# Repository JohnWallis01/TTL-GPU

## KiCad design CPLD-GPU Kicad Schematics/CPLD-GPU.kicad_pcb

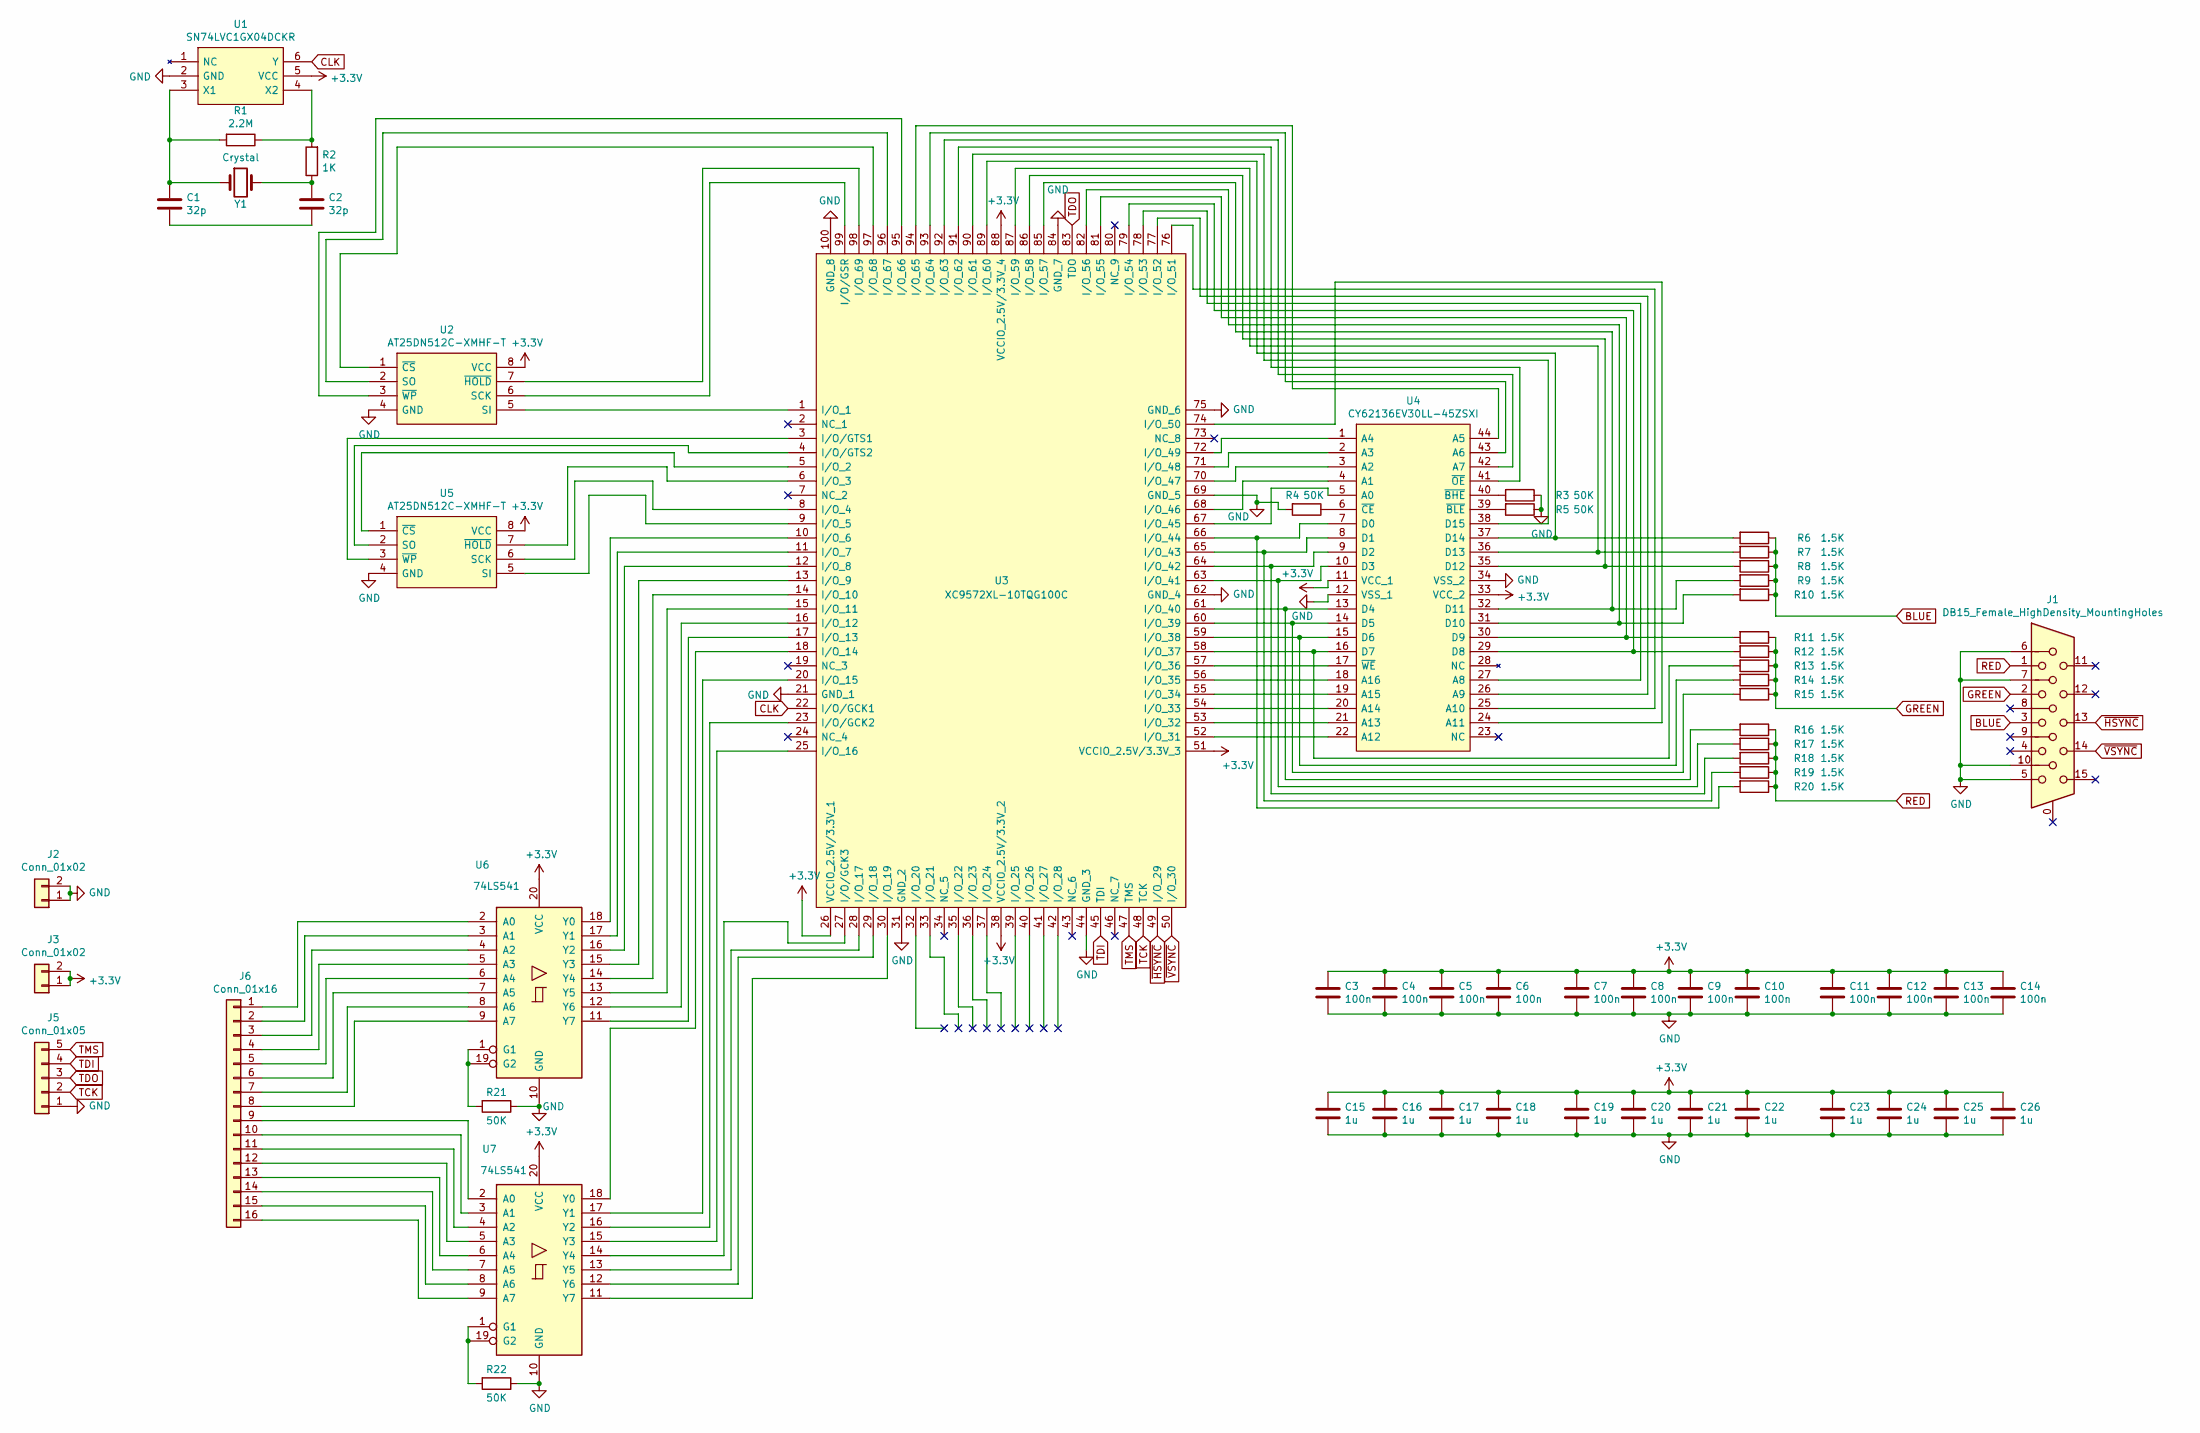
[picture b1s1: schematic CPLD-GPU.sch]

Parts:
C1, C2: 32p; C_0805_2012Metric
C3, C4, C5, C6, C7, C8, C9, C10, C11, C12, C13, C14: 100n; C_0805_2012Metric
C15, C16, C17, C18, C19, C20, C21, C22, C23, C24, C25, C26: 1u; C_0805_2012Metric
J1: DB15_Female_HighDensity_MountingHoles; DSUB-15_Female_Horizontal_P2.77x2.84mm_EdgePinOffset4.94mm_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
J2, J3: Conn_01x02; PinHeader_1x02_P2.54mm_Vertical
J5: Conn_01x05; PinHeader_1x05_P2.54mm_Vertical
J6: Conn_01x16; PinHeader_1x16_P2.54mm_Vertical
R1: 2.2M; R_0805_2012Metric
R2: 1K; R_0805_2012Metric
R3, R4, R5, R21, R22: 50K; R_0805_2012Metric
R6, R7, R8, R9, R10, R11, R12, R13, R14, R15, R16, R17, R18, R19, R20: 1.5K; R_0805_2012Metric
U1: SN74LVC1GX04DCKR; SOT-363_SC-70-6_Handsoldering; Mouser Part Number 595-SN74LVC1GX04DCKR
U2, U5: AT25DN512C-XMHF-T; SSOP-8_2.95x2.8mm_P0.65mm; Manufacturer_Part_Number AT25DN512C-XMHF-T
U3: XC9572XL-10TQG100C; TQFP-100_14x14mm_P0.5mm; Mouser Part Number 217-9572XL-10TQG100C
U4: CY62136EV30LL-45ZSXI; TSOP-II-44_10.16x18.41mm_P0.8mm; Manufacturer_Part_Number CY62136EV30LL-45ZSXI
U6, U7: 74LS541; TSSOP-20_4.4x6.5mm_P0.65mm
Y1: Crystal; Crystal_HC49-4H_Vertical

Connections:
+3V3: C3.1, C4.1, C5.1, C6.1, C7.1, C8.1, C9.1, C10.1, C11.1, C12.1, C13.1, C14.1, C15.1, C16.1, C17.1, C18.1, C19.1, C20.1, C21.1, C22.1, C23.1, C24.1, C25.1, C26.1, J3.1, J3.2, U1.5 (VCC), U2.8 (VCC), U3.26 (VCCIO_2.5V/3.3V_1), U3.38 (VCCIO_2.5V/3.3V_2), U3.51 (VCCIO_2.5V/3.3V_3), U3.88 (VCCIO_2.5V/3.3V_4), U4.11 (VCC_1), U4.33 (VCC_2), U5.8 (VCC), U6.20 (VCC), U7.20 (VCC)
BLUE: J1.3, R6.1, R7.1, R8.1, R9.1, R10.1
CLK: U1.6 (Y), U3.22 (I/O/GCK1)
GND: C3.2, C4.2, C5.2, C6.2, C7.2, C8.2, C9.2, C10.2, C11.2, C12.2, C13.2, C14.2, C15.2, C16.2, C17.2, C18.2, C19.2, C20.2, C21.2, C22.2, C23.2, C24.2, C25.2, C26.2, J1.5, J1.6, J1.7, J1.10, J2.1, J2.2, J5.1, R3.1, R4.2, R5.1, R21.1, R22.1, U1.2 (GND), U2.4 (GND), U3.21 (GND_1), U3.31 (GND_2), U3.44 (GND_3), U3.62 (GND_4), U3.69 (GND_5), U3.75 (GND_6), U3.84 (GND_7), U3.100 (GND_8), U4.12 (VSS_1), U4.34 (VSS_2), U5.4 (GND), U6.10 (GND), U7.10 (GND)
GREEN: J1.2, R11.1, R12.1, R13.1, R14.1, R15.1
unnamed: C1.1, R1.2, U1.3 (X1), Y1.1
unnamed: C1.2, C2.2
unnamed: C2.1, R2.1, Y1.2
unnamed: J6.1, U6.2 (A0)
unnamed: J6.2, U6.3 (A1)
unnamed: J6.3, U6.4 (A2)
unnamed: J6.4, U6.5 (A3)
unnamed: J6.5, U6.6 (A4)
unnamed: J6.6, U6.7 (A5)
unnamed: J6.7, U6.8 (A6)
unnamed: J6.8, U6.9 (A7)
unnamed: J6.9, U7.2 (A0)
unnamed: J6.10, U7.3 (A1)
unnamed: J6.11, U7.4 (A2)
unnamed: J6.12, U7.5 (A3)
unnamed: J6.13, U7.6 (A4)
unnamed: J6.14, U7.7 (A5)
unnamed: J6.15, U7.8 (A6)
unnamed: J6.16, U7.9 (A7)
unnamed: R1.1, R2.2, U1.4 (X2)
unnamed: R3.2, U4.40 (~BHE)
unnamed: R4.1, U4.6 (~CE)
unnamed: R5.2, U4.39 (~BLE)
unnamed: R6.2, U3.89 (I/O_60), U4.37 (D14)
unnamed: R7.2, U3.87 (I/O_59), U4.36 (D13)
unnamed: R8.2, U3.86 (I/O_58), U4.35 (D12)
unnamed: R9.2, U3.85 (I/O_57), U4.32 (D11)
unnamed: R10.2, U3.82 (I/O_56), U4.31 (D10)
unnamed: R11.2, U3.81 (I/O_55), U4.30 (D9)
unnamed: R12.2, U3.79 (I/O_54), U4.29 (D8)
unnamed: R13.2, U3.58 (I/O_37), U4.16 (D7)
unnamed: R14.2, U3.59 (I/O_38), U4.15 (D6)
unnamed: R15.2, U3.60 (I/O_39), U4.14 (D5)
unnamed: R16.2, U3.61 (I/O_40), U4.13 (D4)
unnamed: R17.2, U3.63 (I/O_41), U4.10 (D3)
unnamed: R18.2, U3.64 (I/O_42), U4.9 (D2)
unnamed: R19.2, U3.65 (I/O_43), U4.8 (D1)
unnamed: R20.2, U3.66 (I/O_44), U4.7 (D0)
unnamed: R21.2, U6.1 (G1), U6.19 (G2)
unnamed: R22.2, U7.1 (G1), U7.19 (G2)
unnamed: U2.1 (~CS), U3.97 (I/O_68)
unnamed: U2.2 (SO), U3.96 (I/O_67)
unnamed: U2.3 (~WP), U3.95 (I/O_66)
unnamed: U2.5 (SI), U3.1 (I/O_1)
unnamed: U2.6 (SCK), U3.99 (I/O/GSR)
unnamed: U2.7 (~HOLD), U3.98 (I/O_69)
unnamed: U3.3 (I/O/GTS1), U5.3 (~WP)
unnamed: U3.4 (I/O/GTS2), U5.2 (SO)
unnamed: U3.5 (I/O_2), U5.1 (~CS)
unnamed: U3.6 (I/O_3), U5.7 (~HOLD)
unnamed: U3.8 (I/O_4), U5.6 (SCK)
unnamed: U3.9 (I/O_5), U5.5 (SI)
unnamed: U3.10 (I/O_6), U6.18 (Y0)
unnamed: U3.11 (I/O_7), U6.17 (Y1)
unnamed: U3.12 (I/O_8), U6.16 (Y2)
unnamed: U3.13 (I/O_9), U6.15 (Y3)
unnamed: U3.14 (I/O_10), U6.14 (Y4)
unnamed: U3.15 (I/O_11), U6.13 (Y5)
unnamed: U3.16 (I/O_12), U6.12 (Y6)
unnamed: U3.17 (I/O_13), U6.11 (Y7)
unnamed: U3.18 (I/O_14), U7.18 (Y0)
unnamed: U3.20 (I/O_15), U7.17 (Y1)
unnamed: U3.23 (I/O/GCK2), U7.16 (Y2)
unnamed: U3.25 (I/O_16), U7.15 (Y3)
unnamed: U3.27 (I/O/GCK3), U7.14 (Y4)
unnamed: U3.28 (I/O_17), U7.13 (Y5)
unnamed: U3.29 (I/O_18), U7.12 (Y6)
unnamed: U3.30 (I/O_19), U7.11 (Y7)
unnamed: U3.52 (I/O_31), U4.22 (A12)
unnamed: U3.53 (I/O_32), U4.21 (A13)
unnamed: U3.54 (I/O_33), U4.20 (A14)
unnamed: U3.55 (I/O_34), U4.19 (A15)
unnamed: U3.56 (I/O_35), U4.18 (A16)
unnamed: U3.57 (I/O_36), U4.17 (~WE)
unnamed: U3.67 (I/O_45), U4.5 (A0)
unnamed: U3.68 (I/O_46), U4.4 (A1)
unnamed: U3.70 (I/O_47), U4.3 (A2)
unnamed: U3.71 (I/O_48), U4.2 (A3)
unnamed: U3.72 (I/O_49), U4.1 (A4)
unnamed: U3.74 (I/O_50), U4.24 (A11)
unnamed: U3.76 (I/O_51), U4.25 (A10)
unnamed: U3.77 (I/O_52), U4.26 (A9)
unnamed: U3.78 (I/O_53), U4.27 (A8)
unnamed: U3.90 (I/O_61), U4.38 (D15)
unnamed: U3.91 (I/O_62), U4.41 (~OE)
unnamed: U3.92 (I/O_63), U4.42 (A7)
unnamed: U3.93 (I/O_64), U4.43 (A6)
unnamed: U3.94 (I/O_65), U4.44 (A5)
RED: J1.1, R16.1, R17.1, R18.1, R19.1, R20.1
TCK: J5.2, U3.48 (TCK)
TDI: J5.4, U3.45 (TDI)
TDO: J5.3, U3.83 (TDO)
TMS: J5.5, U3.47 (TMS)
~HSYNC: J1.13, U3.49 (I/O_29)
~VSYNC: J1.14, U3.50 (I/O_30)

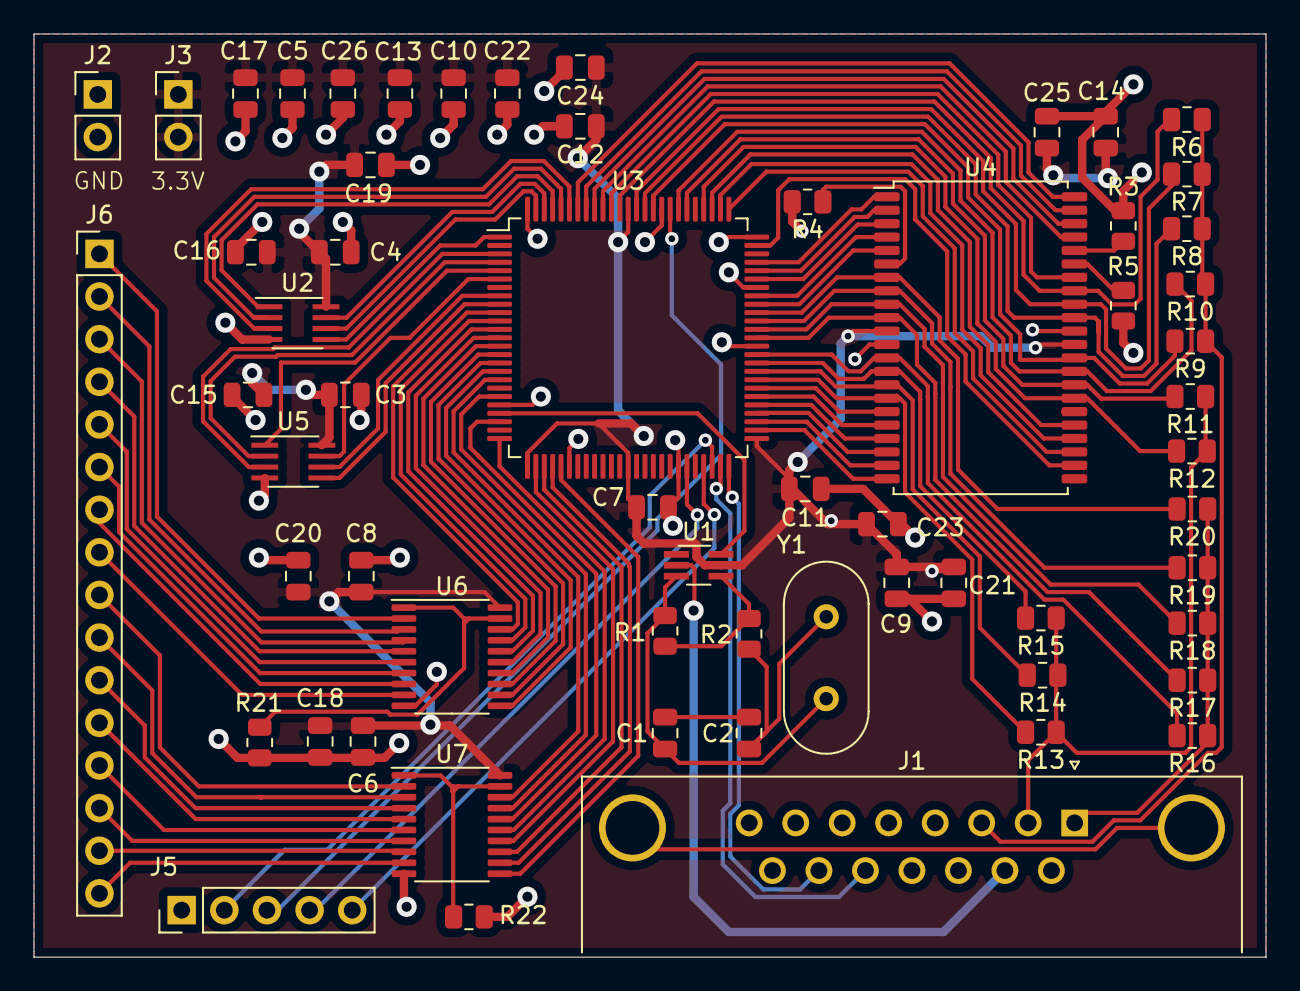
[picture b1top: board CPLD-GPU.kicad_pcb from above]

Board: 2 copper layers, 73.4 x 55.0 mm, 61 parts (0 on the bottom side), 100 nets.

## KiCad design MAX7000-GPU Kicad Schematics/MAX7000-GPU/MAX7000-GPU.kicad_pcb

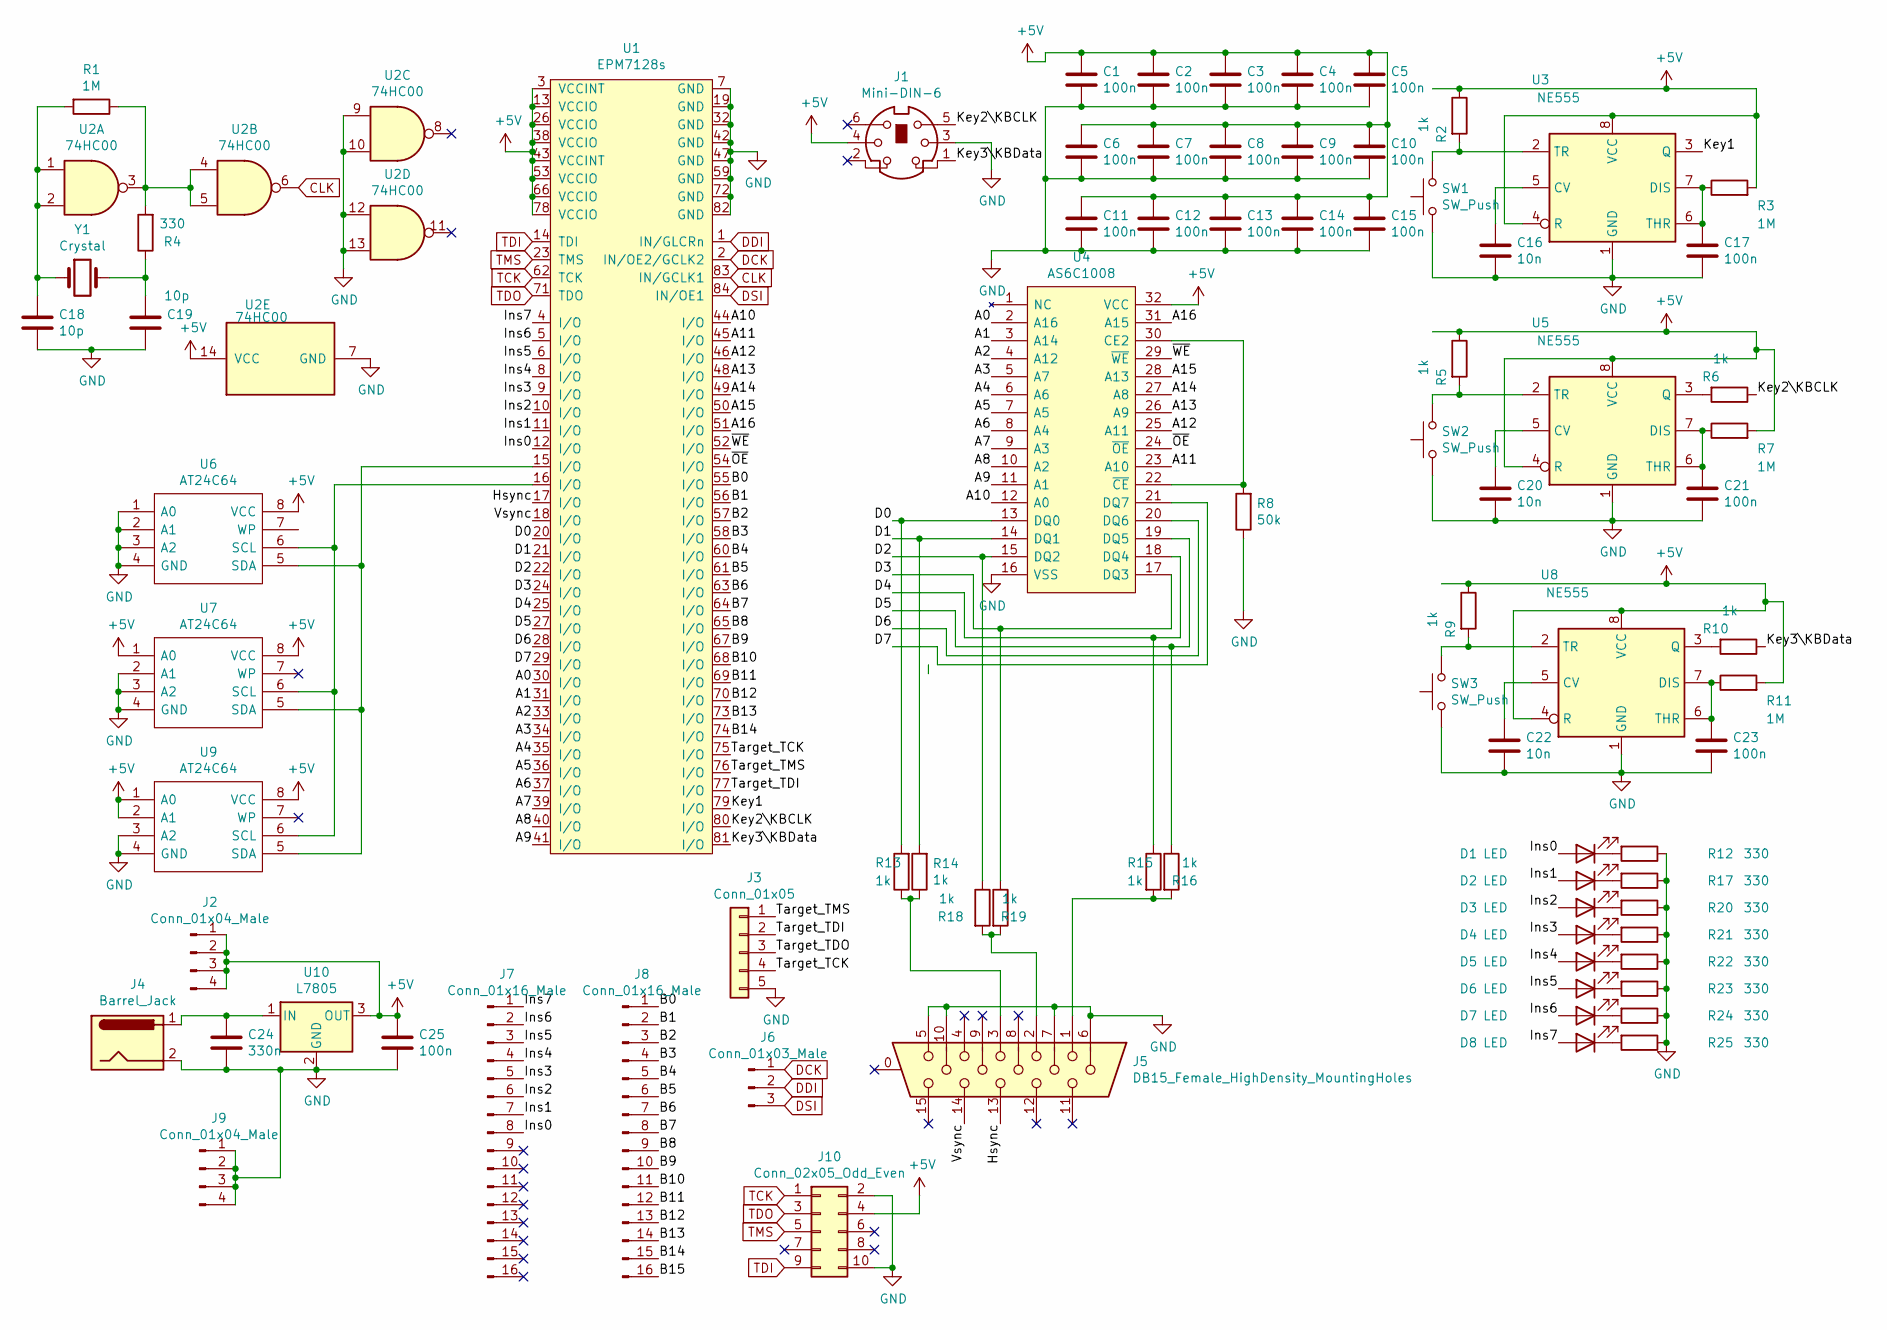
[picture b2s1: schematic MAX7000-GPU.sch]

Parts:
C1, C2, C3, C4, C5, C6, C7, C8, C9, C10, C11, C12, C13, C14, C15, C17, C21, C23, C25: 100n; C_0805_2012Metric
C16, C20, C22: 10n; C_0805_2012Metric
C18, C19: 10p; C_0805_2012Metric
C24: 330n; C_0805_2012Metric
D1, D2, D3, D4, D5, D6, D7, D8: LED; LED_0805_2012Metric
J1: Mini-DIN-6; Connector_Mini-DIN_Female_6Pin_2rows
J2, J9: Conn_01x04_Male; PinSocket_1x04_P2.54mm_Vertical
J3: Conn_01x05; PinSocket_1x05_P2.54mm_Vertical
J4: Barrel_Jack; BarrelJack_Wuerth_6941xx301002
J5: DB15_Female_HighDensity_MountingHoles; DSUB-15-HD_Female_Horizontal_P2.29x1.98mm_EdgePinOffset3.03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
J6: Conn_01x03_Male; PinSocket_1x03_P2.54mm_Vertical
J7, J8: Conn_01x16_Male; PinSocket_1x16_P2.54mm_Vertical
J10: Conn_02x05_Odd_Even; PinHeader_2x05_P2.54mm_Vertical
R1, R3, R7, R11: 1M; R_0805_2012Metric
R2, R5, R6, R9, R10, R13, R14, R15, R16, R18, R19: 1k; R_0805_2012Metric
R4, R12, R17, R20, R21, R22, R23, R24, R25: 330; R_0805_2012Metric
R8: 50k; R_0805_2012Metric
SW1, SW2, SW3: SW_Push; SW_PUSH_6mm
U1: EPM7128s; PLCC-84_THT-Socket
U2: 74HC00; DIP-14_W7.62mm
U3, U5, U8: NE555; DIP-8_W7.62mm
U4: AS6C1008; DIP-32_W15.24mm; Mouser Part Number 913-AS6C1008-55PCN
U6, U7, U9: AT24C64; DIP-8_W7.62mm; Manufacturer_Part_Number AT24C64B-10PU-2.7
U10: L7805; TO-220-3_Vertical
Y1: Crystal; Crystal_HC49-U_Vertical

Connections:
+5V: C1.1, C2.1, C3.1, C4.1, C5.1, C6.1, C7.1, C8.1, C9.1, C10.1, C11.1, C12.1, C13.1, C14.1, C15.1, C25.1, J1.4, J2.1, J2.2, J2.3, J2.4, J10.4, R2.1, R3.2, R5.1, R7.2, R9.1, R11.2, U1.3 (VCCINT), U1.13 (VCCIO), U1.26 (VCCIO), U1.38 (VCCIO), U1.43 (VCCINT), U1.53 (VCCIO), U1.66 (VCCIO), U1.78 (VCCIO), U2.14 (VCC), U3.4 (R), U3.8 (VCC), U4.32 (VCC), U5.4 (R), U5.8 (VCC), U6.8 (VCC), U7.1 (A0), U7.8 (VCC), U8.4 (R), U8.8 (VCC), U9.1 (A0), U9.2 (A1), U9.8 (VCC), U10.3 (OUT)
/A0: U1.30 (I/O), U4.2 (A16)
/A1: U1.31 (I/O), U4.3 (A14)
/A2: U1.33 (I/O), U4.4 (A12)
/A3: U1.34 (I/O), U4.5 (A7)
/A4: U1.35 (I/O), U4.6 (A6)
/A5: U1.36 (I/O), U4.7 (A5)
/A6: U1.37 (I/O), U4.8 (A4)
/A7: U1.39 (I/O), U4.9 (A3)
/A8: U1.40 (I/O), U4.10 (A2)
/A9: U1.41 (I/O), U4.11 (A1)
/A10: U1.44 (I/O), U4.12 (A0)
/A11: U1.45 (I/O), U4.23 (A10)
/A12: U1.46 (I/O), U4.25 (A11)
/A13: U1.48 (I/O), U4.26 (A9)
/A14: U1.49 (I/O), U4.27 (A8)
/A15: U1.50 (I/O), U4.28 (A13)
/A16: U1.51 (I/O), U4.31 (A15)
/B0: J8.1, U1.55 (I/O)
/B1: J8.2, U1.56 (I/O)
/B2: J8.3, U1.57 (I/O)
/B3: J8.4, U1.58 (I/O)
/B4: J8.5, U1.60 (I/O)
/B5: J8.6, U1.61 (I/O)
/B6: J8.7, U1.63 (I/O)
/B7: J8.8, U1.64 (I/O)
/B8: J8.9, U1.65 (I/O)
/B9: J8.10, U1.67 (I/O)
/B10: J8.11, U1.68 (I/O)
/B11: J8.12, U1.69 (I/O)
/B12: J8.13, U1.70 (I/O)
/B13: J8.14, U1.73 (I/O)
/B14: J8.15, U1.74 (I/O)
/D0: R13.2, U1.20 (I/O), U4.13 (DQ0)
/D1: R14.2, U1.21 (I/O), U4.14 (DQ1)
/D2: R18.1, U1.22 (I/O), U4.15 (DQ2)
/D3: R19.1, U1.24 (I/O), U4.17 (DQ3)
/D4: R15.1, U1.25 (I/O), U4.18 (DQ4)
/D5: R16.1, U1.27 (I/O), U4.19 (DQ5)
/D6: U1.28 (I/O), U4.20 (DQ6)
/D7: U1.29 (I/O), U4.21 (DQ7)
/Hsync: J5.13, U1.17 (I/O)
/Ins0: D1.2 (A), J7.8, U1.12 (I/O)
/Ins1: D2.2 (A), J7.7, U1.11 (I/O)
/Ins2: D3.2 (A), J7.6, U1.10 (I/O)
/Ins3: D4.2 (A), J7.5, U1.9 (I/O)
/Ins4: D5.2 (A), J7.4, U1.8 (I/O)
/Ins5: D6.2 (A), J7.3, U1.6 (I/O)
/Ins6: D7.2 (A), J7.2, U1.5 (I/O)
/Ins7: D8.2 (A), J7.1, U1.4 (I/O)
/Key1: U1.79 (I/O), U3.3 (Q)
/Key2\KBCLK: J1.5, R6.1, U1.80 (I/O)
/Key3\KBData: J1.1, R10.1, U1.81 (I/O)
/Target_TCK: J3.4, U1.75 (I/O)
/Target_TDI: J3.2, U1.77 (I/O)
/Target_TMS: J3.1, U1.76 (I/O)
/Vsync: J5.14, U1.18 (I/O)
/~OE: U1.54 (I/O), U4.24 (~OE)
/~WE: U1.52 (I/O), U4.29 (~WE)
CLK: U1.83 (IN/GCLK1), U2.6
DCK: J6.1, U1.2 (IN/OE2/GCLK2)
DDI: J6.2, U1.1 (IN/GLCRn)
DSI: J6.3, U1.84 (IN/OE1)
GND: C1.2, C2.2, C3.2, C4.2, C5.2, C6.2, C7.2, C8.2, C9.2, C10.2, C11.2, C12.2, C13.2, C14.2, C15.2, C16.2, C17.2, C18.2, C19.2, C20.2, C21.2, C22.2, C23.2, C24.2, C25.2, J1.3, J3.5, J4.2, J5.5, J5.6, J5.7, J5.10, J9.1, J9.2, J9.3, J9.4, J10.2, J10.10, R8.1, R12.1, R17.1, R20.1, R21.1, R22.1, R23.1, R24.1, R25.1, SW1.1, SW2.1, SW3.1, U1.7 (GND), U1.19 (GND), U1.32 (GND), U1.42 (GND), U1.47 (GND), U1.59 (GND), U1.72 (GND), U1.82 (GND), U2.7 (GND), U2.9, U2.10, U2.12, U2.13, U3.1 (GND), U4.16 (VSS), U5.1 (GND), U6.1 (A0), U6.2 (A1), U6.3 (A2), U6.4 (GND), U7.2 (A1), U7.3 (A2), U7.4 (GND), U8.1 (GND), U9.3 (A2), U9.4 (GND), U10.2 (GND)
unnamed: C16.1, U3.5 (CV)
unnamed: C17.1, R3.1, U3.6 (THR), U3.7 (DIS)
unnamed: C18.1, R1.2, U2.1, U2.2, Y1.1
unnamed: C19.1, R4.1, Y1.2
unnamed: C20.1, U5.5 (CV)
unnamed: C21.1, R7.1, U5.6 (THR), U5.7 (DIS)
unnamed: C22.1, U8.5 (CV)
unnamed: C23.1, R11.1, U8.6 (THR), U8.7 (DIS)
unnamed: C24.1, J4.1, U10.1 (IN)
unnamed: D1.1 (K), R12.2
unnamed: D2.1 (K), R17.2
unnamed: D3.1 (K), R20.2
unnamed: D4.1 (K), R21.2
unnamed: D5.1 (K), R22.2
unnamed: D6.1 (K), R23.2
unnamed: D7.1 (K), R24.2
unnamed: D8.1 (K), R25.2
unnamed: J5.1, R15.2, R16.2
unnamed: J5.2, R18.2, R19.2
unnamed: J5.3, R13.1, R14.1
unnamed: R1.1, R4.2, U2.3, U2.4, U2.5
unnamed: R2.2, SW1.2, U3.2 (TR)
unnamed: R5.2, SW2.2, U5.2 (TR)
unnamed: R6.2, U5.3 (Q)
unnamed: R8.2, U4.22 (~CE), U4.30 (CE2)
unnamed: R9.2, SW3.2, U8.2 (TR)
unnamed: R10.2, U8.3 (Q)
unnamed: U1.15 (I/O), U6.5 (SDA), U7.5 (SDA), U9.5 (SDA)
unnamed: U1.16 (I/O), U6.6 (SCL), U7.6 (SCL), U9.6 (SCL)
TCK: J10.1, U1.62 (TCK)
TDI: J10.9, U1.14 (TDI)
TDO: J10.3, U1.71 (TDO)
TMS: J10.5, U1.23 (TMS)

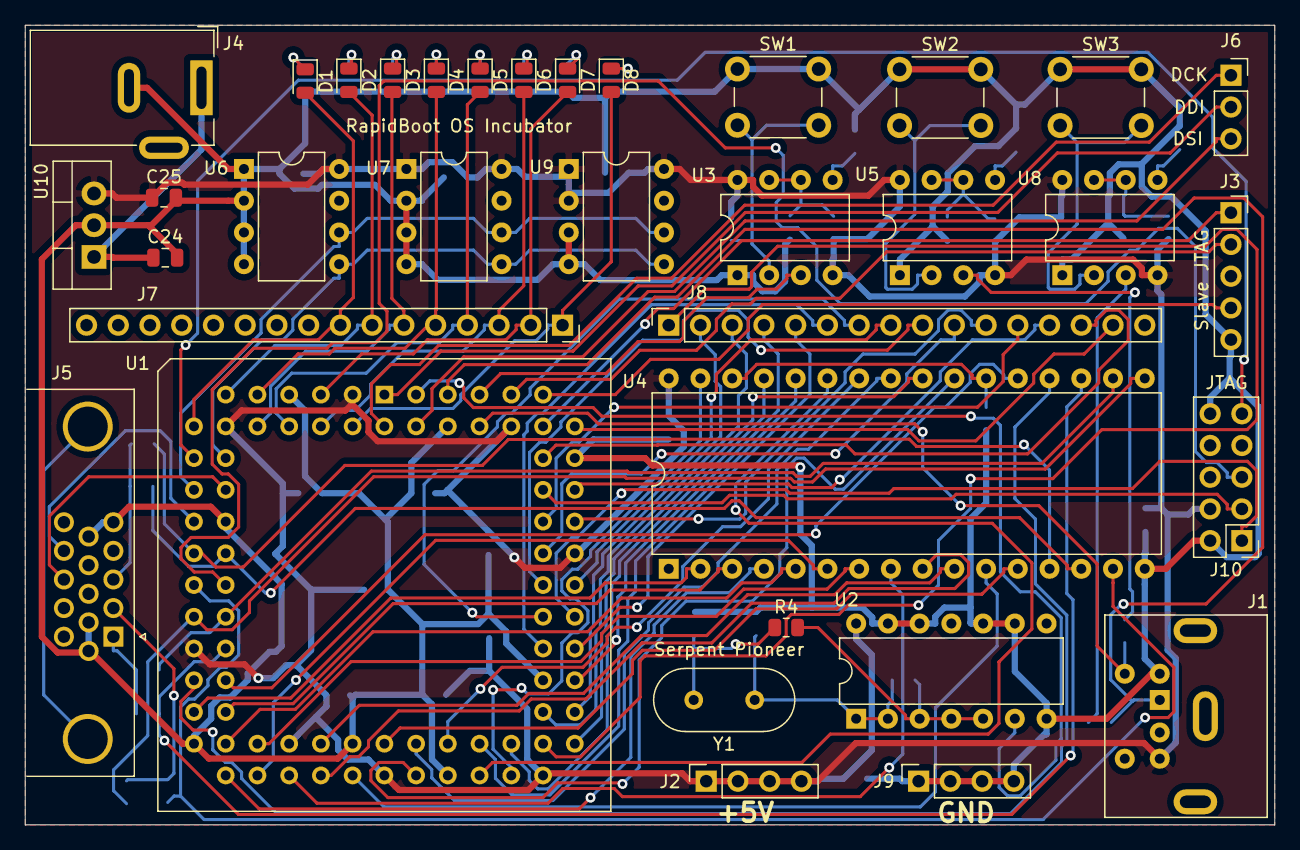
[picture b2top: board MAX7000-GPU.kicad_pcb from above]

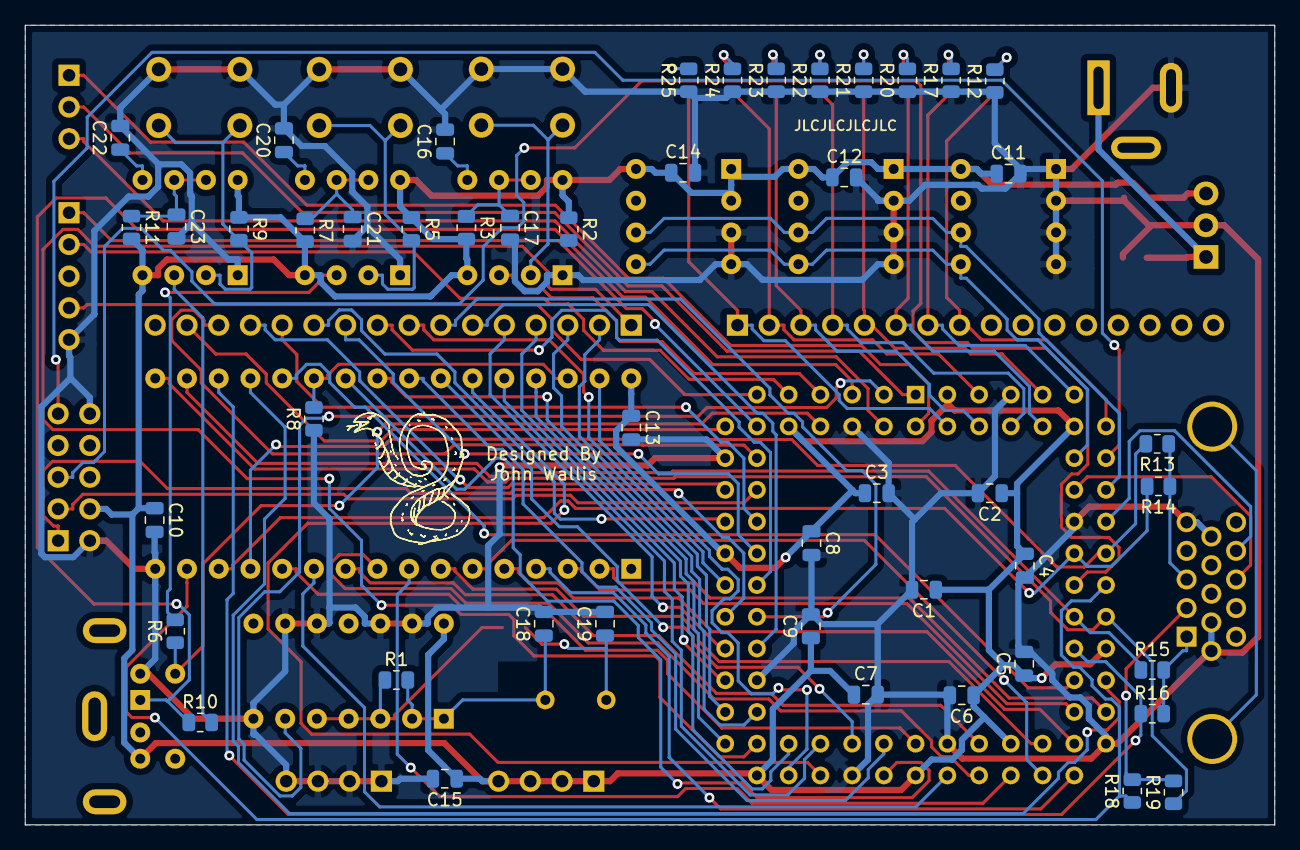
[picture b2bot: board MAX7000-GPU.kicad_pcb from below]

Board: 2 copper layers, 100.0 x 64.0 mm, 82 parts (47 on the bottom side), 97 nets.

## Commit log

2022-04-17 Inital Commit
2022-04-17 Bom Updates
